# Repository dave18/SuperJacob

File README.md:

# SuperJacob
SuperJacob Hobby Computer

Design files are for Eagle

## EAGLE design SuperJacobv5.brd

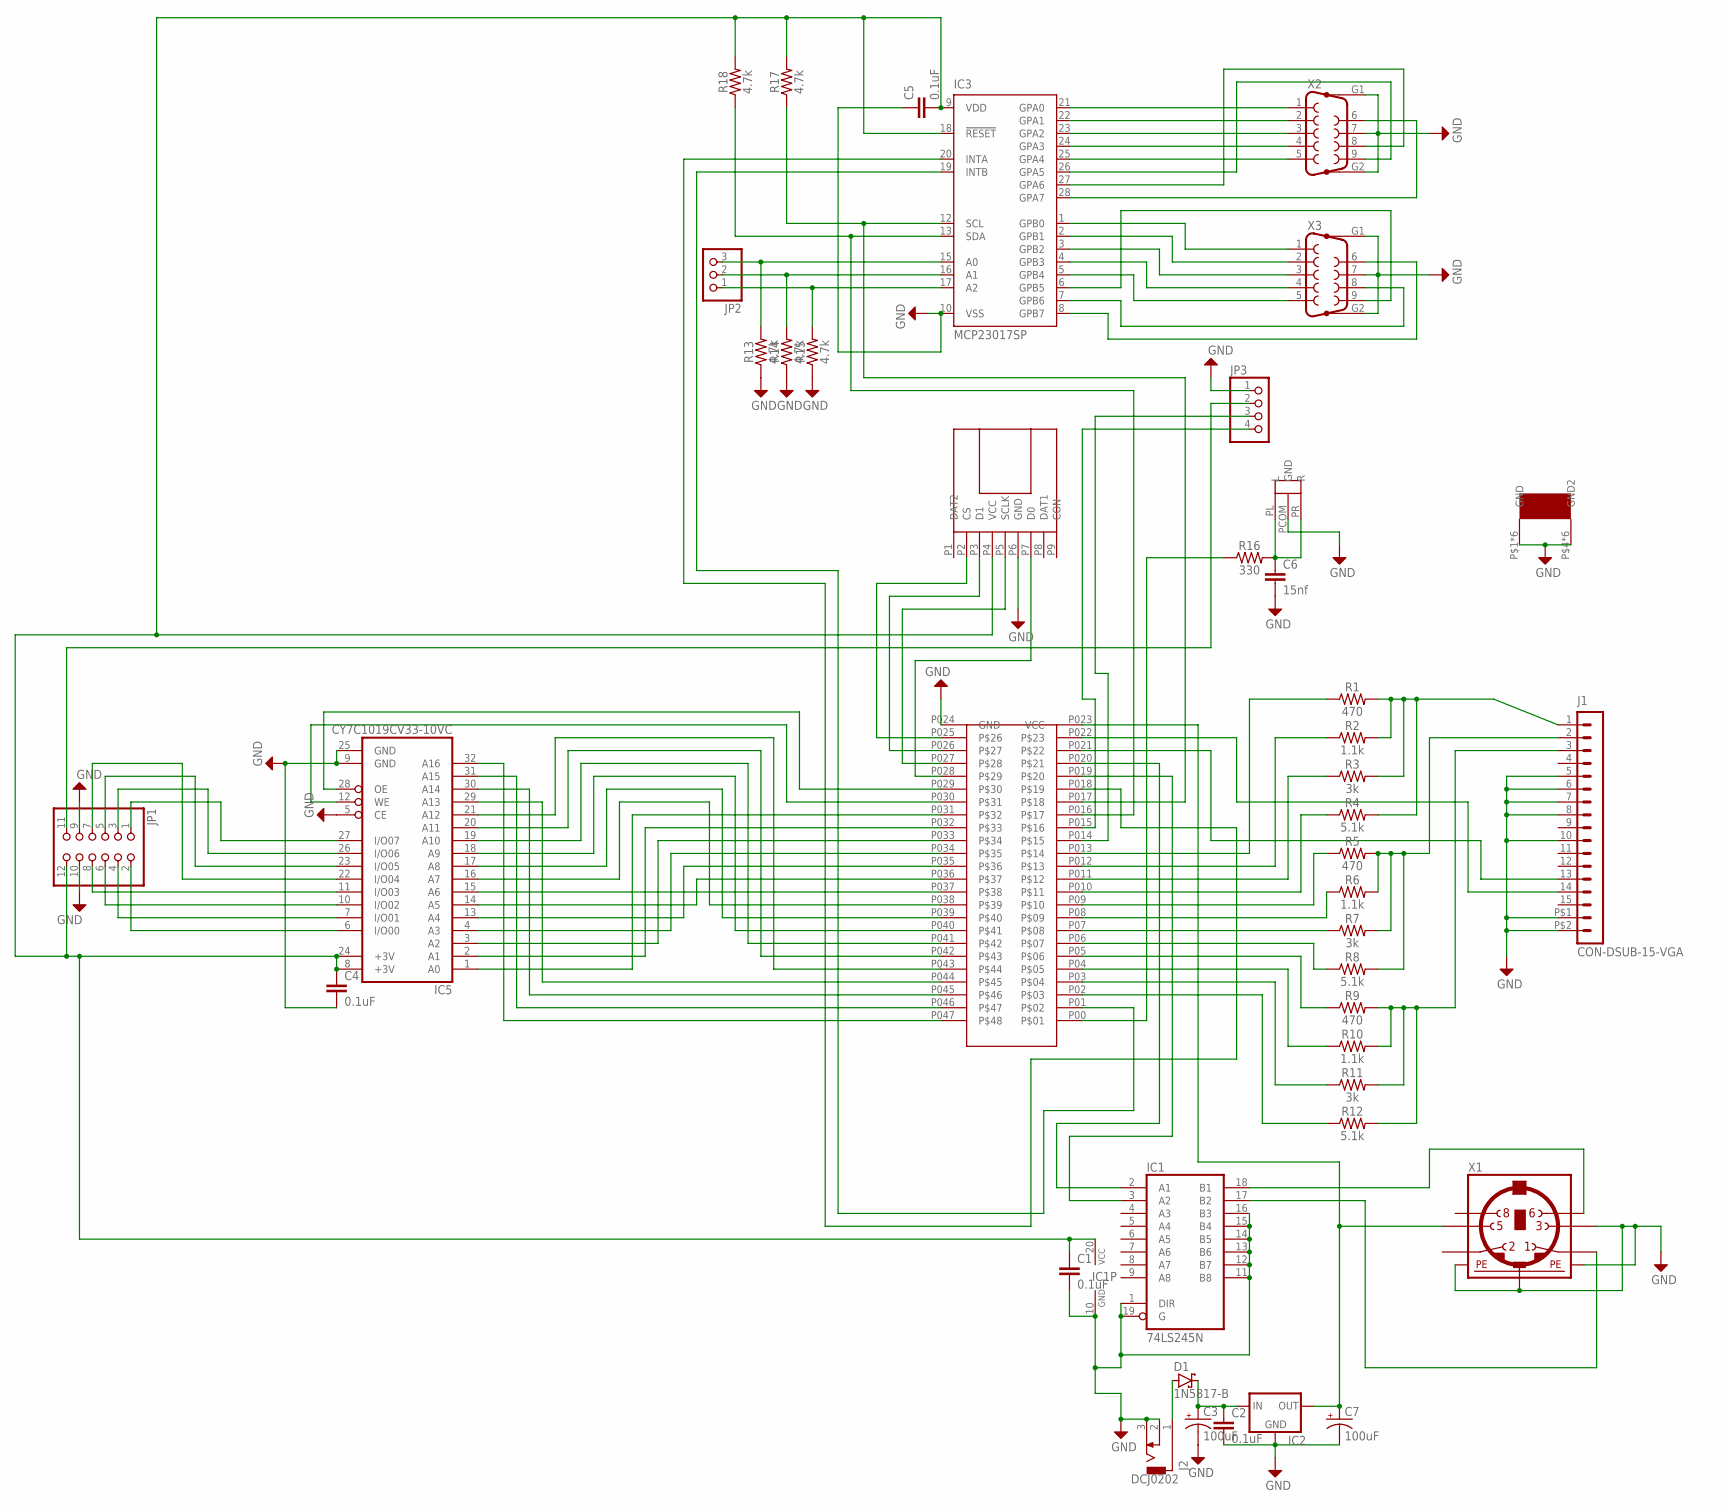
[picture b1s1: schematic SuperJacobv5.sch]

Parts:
C1, C2, C4, C5: 0.1uF; CAP-PTH-SMALL-KIT
C3, C7: 100uF; CPOL-RADIAL-2.5MM-5MM
C6: 15nf; CAP-PTH-SMALL-KIT
D1: 1N5817-B; DO41-7.6
IC1: 74LS245N; DIL20
IC2: 78XXL
IC3: MCP23017SP; DIL28-3
IC5: CY7C1019CV33-10VC; SOJ32-400
J1: CON-DSUB-15-VGA; 181-015-212-171
J2: DCJ0202
JP1: PINHD-2X6; 2X06
JP2: PINHD-1X3; 1X03
JP3: PINHD-1X4; 1X04
R1, R5, R9: 470; AXIAL-0.3
R2, R6, R10: 1.1k; AXIAL-0.3
R3, R7, R11: 3k; AXIAL-0.3
R4, R8, R12: 5.1k; AXIAL-0.3
R13, R14, R15, R17, R18: 4.7k; AXIAL-0.3
R16: 330; AXIAL-0.3
U$1: CMODA7
U$2: OPEN-SMARTTFCARDBREAKOUT
U$3: AUDIOJACK
U$4: 7085THERMALPAD; 7805THERMALPAD
X1: MINI_DIN_6; M_DIN6
X2, X3: F09HP

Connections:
+5V: C7.1 (+), IC2.OUT, U$1.P023 (VCC), X1.5
ANLGPAD1: JP3.3, U$1.P014
ANLGPAD2: JP3.4, U$1.P015
AUDIOPOSTFILTER: C6.1, R16.P$2 (2), U$3.PL (L), U$3.PR (R)
AUDIOPREFILTER: R16.P$1 (1), U$1.P00
BLUE: J1.3, R9.P$2 (2), R10.P$2 (2), R11.P$2 (2), R12.P$2 (2)
BLUEBIT0: R12.P$1 (1), U$1.P02
BLUEBIT1: R11.P$1 (1), U$1.P03
BLUEBIT2: R10.P$1 (1), U$1.P04
BLUEBIT3: R9.P$1 (1), U$1.P05
GND: C1.2, C2.2, C3.2 (-), C4.2, C5.1, C6.2, C7.2 (-), IC1.1 (DIR), IC1.10 (GND), IC1.11 (B8), IC1.12 (B7), IC1.13 (B6), IC1.14 (B5), IC1.15 (B4), IC1.16 (B3), IC1.19 (G), IC2.GND, IC3.10 (VSS), IC5.5 (CE), IC5.9 (GND), IC5.25 (GND), J1.5, J1.6, J1.7, J1.8, J1.10, J1.P$1 (16), J1.P$2 (17), J2.2, J2.3, JP1.9, JP1.10, JP3.1, R13.P$1 (1), R14.P$1 (1), R15.P$1 (1), U$1.P024 (GND), U$2.P6 (GND), U$3.PCOM (GND), U$4.P$1 (GND), U$4.P$4 (GND2), U$4.P$6 (GND), U$4.P$7 (GND), U$4.P$8 (GND), U$4.P$9 (GND), U$4.P$10 (GND), U$4.P$11 (GND2), U$4.P$14 (GND2), U$4.P$19 (GND2), U$4.P$21 (GND2), U$4.P$24 (GND2), X1.3, X1.SH1 (PE1), X1.SH2 (PE2), X1.SH3 (PE3), X2.7, X2.G1, X2.G2, X3.7, X3.G1, X3.G2
GPIOCLK: IC3.12 (SCL), R17.P$1 (1), U$1.P017
GPIODATA: IC3.13 (SDA), R18.P$1 (1), U$1.P016
GPIOINTA: IC3.20 (INTA), U$1.P018
GPIOINTB: IC3.19 (INTB), U$1.P01
GREEN: J1.2, R5.P$2 (2), R6.P$2 (2), R7.P$2 (2), R8.P$2 (2)
GREENBIT0: R8.P$1 (1), U$1.P06
GREENBIT1: R7.P$1 (1), U$1.P07
GREENBIT2: R6.P$1 (1), U$1.P08
GREENBIT3: R5.P$1 (1), U$1.P09
HSYNC: J1.13, U$1.P021
IOADDR0: IC3.15 (A0), JP2.3, R13.P$2 (2)
IOADDR1: IC3.16 (A1), JP2.2, R14.P$2 (2)
IOADDR2: IC3.17 (A2), JP2.1, R15.P$2 (2)
JOY1DOWN: IC3.24 (GPA3), X2.4
JOY1FIRE: IC3.26 (GPA5), X2.9
JOY1LEFT: IC3.23 (GPA2), X2.3
JOY1RIGHT: IC3.22 (GPA1), X2.2
JOY1SPARE1: IC3.21 (GPA0), X2.1
JOY1SPARE2: IC3.27 (GPA6), X2.8
JOY1SPARE3: IC3.28 (GPA7), X2.6
JOY1UP: IC3.25 (GPA4), X2.5
JOY2DOWN: IC3.4 (GPB3), X3.4
JOY2FIRE: IC3.6 (GPB5), X3.9
JOY2LEFT: IC3.3 (GPB2), X3.3
JOY2RIGHT: IC3.2 (GPB1), X3.2
JOY2SPARE1: IC3.1 (GPB0), X3.1
JOY2SPARE2: IC3.7 (GPB6), X3.8
JOY2SPARE3: IC3.8 (GPB7), X3.6
JOY2UP: IC3.5 (GPB4), X3.5
KBCLK: IC1.18 (B1), X1.6
KBCLK33V: IC1.2 (A1), U$1.P020
KBDATA: IC1.17 (B2), X1.1
KBDATA33V: IC1.3 (A2), U$1.P019
unnamed: D1.A, J2.1
POWERIN: C2.1, C3.1 (+), D1.C, IC2.IN
RAM10: IC5.19 (A10), U$1.P041
RAM11: IC5.20 (A11), U$1.P042
RAMA0: IC5.1 (A0), U$1.P031
RAMA1: IC5.2 (A1), U$1.P032
RAMA2: IC5.3 (A2), U$1.P033
RAMA3: IC5.4 (A3), U$1.P034
RAMA4: IC5.13 (A4), U$1.P035
RAMA5: IC5.14 (A5), U$1.P036
RAMA6: IC5.15 (A6), U$1.P037
RAMA7: IC5.16 (A7), U$1.P038
RAMA8: IC5.17 (A8), U$1.P039
RAMA9: IC5.18 (A9), U$1.P040
RAMA12: IC5.21 (A12), U$1.P043
RAMA13: IC5.29 (A13), U$1.P044
RAMA14: IC5.30 (A14), U$1.P045
RAMA15: IC5.31 (A15), U$1.P046
RAMA16: IC5.32 (A16), U$1.P047
RAMIO0: IC5.6 (I/O00), JP1.2
RAMIO1: IC5.7 (I/O01), JP1.4
RAMIO2: IC5.10 (I/O02), JP1.6
RAMIO3: IC5.11 (I/O03), JP1.8
RAMIO4: IC5.22 (I/O04), JP1.7
RAMIO5: IC5.23 (I/O05), JP1.5
RAMIO6: IC5.26 (I/O06), JP1.3
RAMIO7: IC5.27 (I/O07), JP1.1
RAMOE: IC5.28 (OE), U$1.P029
RAMWE: IC5.12 (WE), U$1.P030
RED: J1.1, R1.P$2 (2), R2.P$2 (2), R3.P$2 (2), R4.P$2 (2)
REDBIT0: R4.P$1 (1), U$1.P010
REDBIT1: R3.P$1 (1), U$1.P011
REDBIT2: R2.P$1 (1), U$1.P012
REDBIT3: R1.P$1 (1), U$1.P013
SDCLK: U$1.P027, U$2.P5 (SCLK)
SDCS: U$1.P025, U$2.P2 (CS)
SDD0: U$1.P028, U$2.P7 (D0)
SDD1: U$1.P026, U$2.P3 (D1)
VCC3.3V-EXT: JP1.11, JP3.2
VCC+3.3V: C1.1, C4.1, C5.2, IC1.20 (VCC), IC3.9 (VDD), IC3.18 (!RESET), IC5.8 (+3V), IC5.24 (+3V), JP1.12, R17.P$2 (2), R18.P$2 (2), U$2.P4 (VCC)
VSYNC: J1.14, U$1.P022

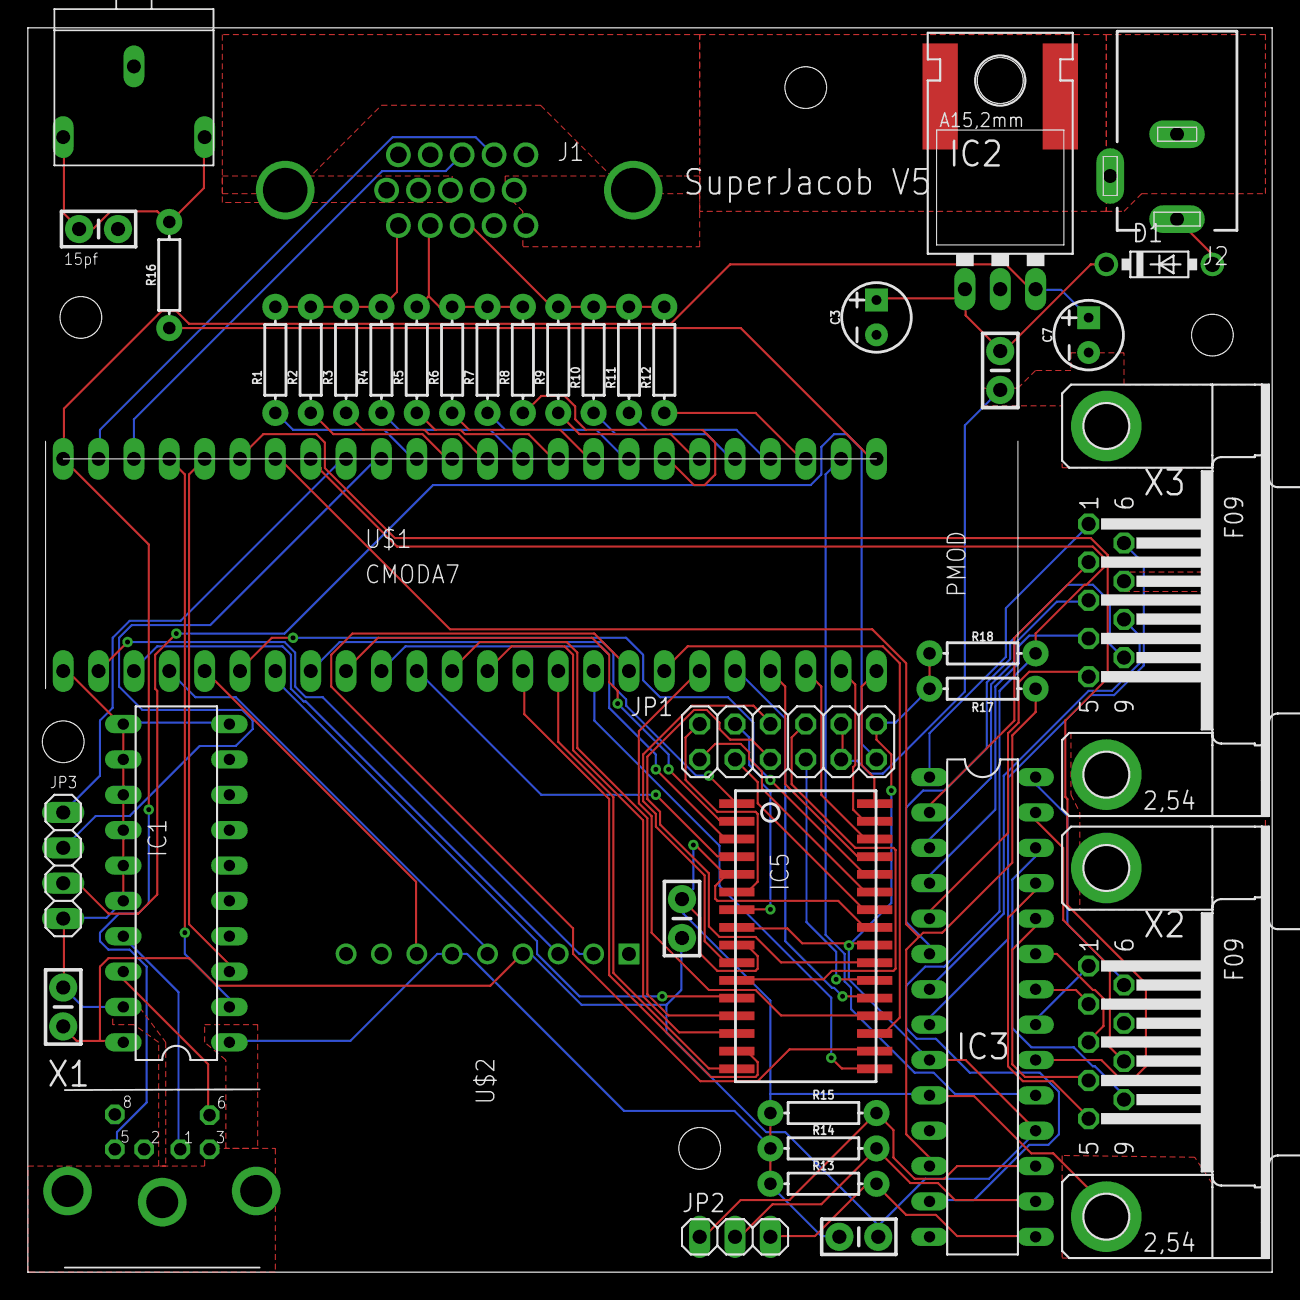
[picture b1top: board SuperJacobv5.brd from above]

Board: 2 copper layers, 89.4 x 89.4 mm, 42 parts (0 on the bottom side), 85 nets.

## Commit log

2020-12-23 Upload Hardware Files

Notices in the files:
parts and their libraries:
m-pad-2.1: License : GNU General Public License version 2 (see bottom)
SparkFun-Resistors: Licensing: Creative Commons ShareAlike 4.0 International - https://creativecommons.org/licenses/by-sa/4.0
